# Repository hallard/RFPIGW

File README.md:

RFM12B RFM69CW Raspberry Pi Gateway With OLED and OOK
=====================================================

This is a simple board to be able to 
- Receive RFM12B data
- Receive RFM69CW data
- Blink 1st led when receiving from 1st module
- Blink 2nd led when receiving from 2nd module
- Display whatever on I2C OLED LCD
- Ready for OOK send/receive (see [jeelabs][5] for how to)

This is the 2nd proto board, I've ordered one on OSHPark, assembled 
then and it works fine so far. In this new version I've flipped the 
OLED since on some enclosure it was impossible to close them due to 
the total thickness of the board + OLED over it.

This version replace the 1.1 version which had some wiring reversed 
(MOSI/MISO) on the bottom module. I've also put the crystal on top 
side of the PCB instead of the bottom

No firmware or documentation is released because I'm currently working on 
project that will use this board as a gateway and I will release all source
code and documentation in the same time.
But you can take a look to this new project [Ultra Low Power Wireless Arduino Node][3]

This board gateway should work with the official firmware of [RFM2PI][6]
board dedicated for emoncms with small tweaking.

Check out news and other projects on my [blog][4]

Detailed Description
====================

Everything will be documented on my [blog][4]

**Schematic**  

**Boards**  
&nbsp;
&nbsp;

[3]: http://hallard.me/bp-ulpnode/
[4]: http://hallard.me
[5]: http://jeelabs.net/projects/cafe/wiki/Receiving_OOKASK_with_a_modified_RFM12B
[6]: http://wiki.openenergymonitor.org/index.php?title=RFM12Pi_V2

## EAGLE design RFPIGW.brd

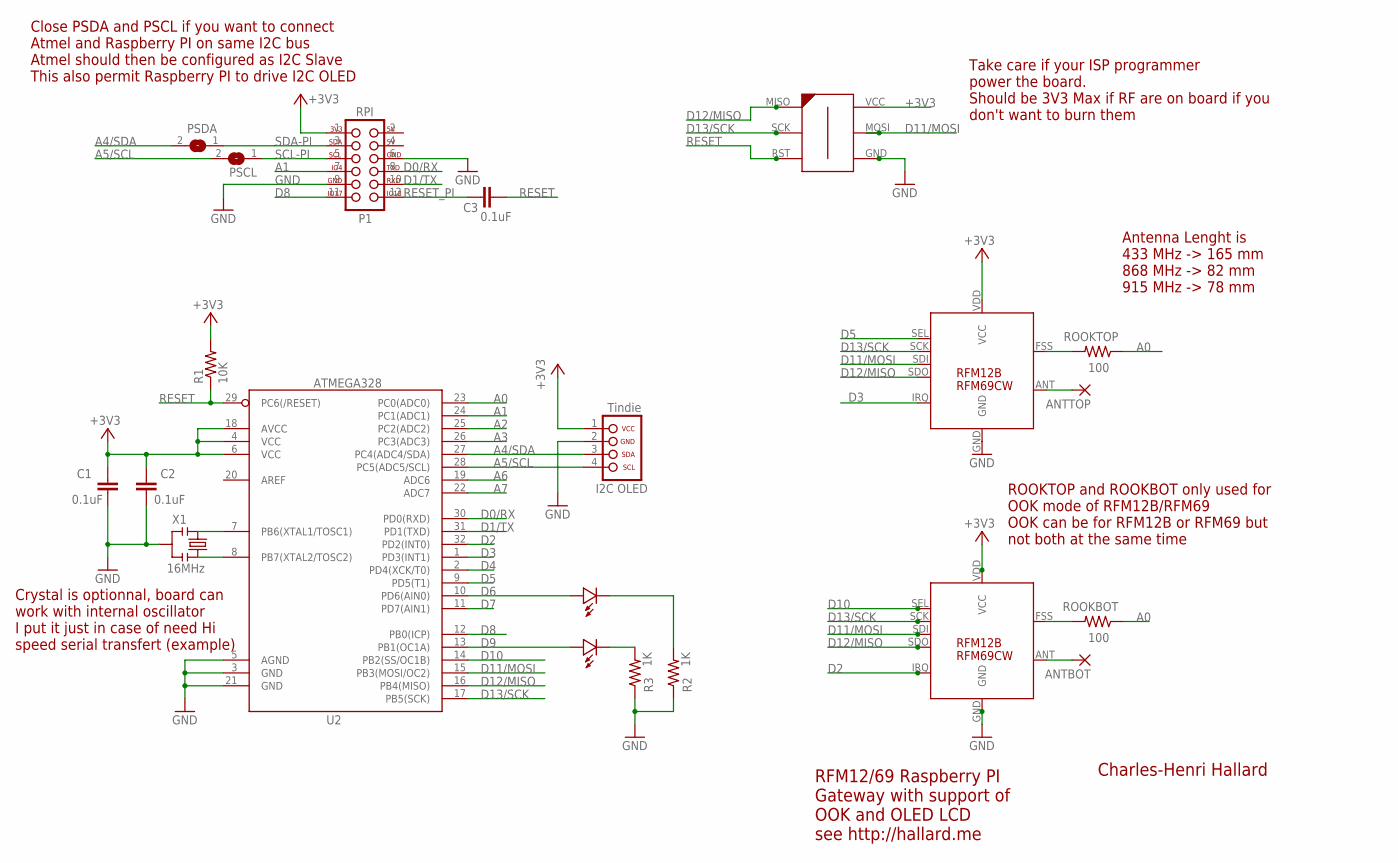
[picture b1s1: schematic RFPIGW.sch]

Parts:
ANTBOT: 1,6/0,8
ANTTOP: 1,6/0,8
C1, C2, C3: 0.1uF; 0805-CAP
LED1, LED2: LED0805-LARGE; 0805-LED-LARGEPADS
OLED: OLED_I2C_TINDIE; 1X04_NO_LOCK
PSCL: SJ
PSDA: SJ
R1: 10K; 0805-RES
R2, R3: 1K; 0805-RES
ROOKBOT: 100; 0805-RES
ROOKTOP: 100; 0805-RES
U2: ATMEGA328; TQFP32-08
U$1: PI P1; 2X06_LOCK
U$2, U$3: RFM12B; RFM12B-MINPADS
U$4: AVR-ISP-6-EDGE; 6PAD_ISP
X1: 16MHz; RESONATOR-SMD

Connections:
2: U$1.2
4: U$1.4
+3V3: C1.1, C2.1, OLED.1 (VCC), R1.2, U2.4 (VCC), U2.6 (VCC), U2.18 (AVCC), U$1.1, U$2.VDD (VCC), U$3.VDD (VCC), U$4.VCC
A0: ROOKBOT.1, ROOKTOP.1, U2.23 (PC0(ADC0))
A1: U2.24 (PC1(ADC1)), U$1.7
A2: U2.25 (PC2(ADC2))
A3: U2.26 (PC3(ADC3))
A4/SDA: OLED.3 (SDA), PSDA.2, U2.27 (PC4(ADC4/SDA))
A5/SCL: OLED.4 (SCL), PSCL.2, U2.28 (PC5(ADC5/SCL))
A6: U2.19 (ADC6)
A7: U2.22 (ADC7)
D0/RX: U2.30 (PD0(RXD)), U$1.8
D1/TX: U2.31 (PD1(TXD)), U$1.10
D2: U2.32 (PD2(INT0)), U$2.IRQ
D3: U2.1 (PD3(INT1)), U$3.IRQ
D4: U2.2 (PD4(XCK/T0))
D5: U2.9 (PD5(T1)), U$3.SEL
D6: LED2.PLUS, U2.10 (PD6(AIN0))
D7: U2.11 (PD7(AIN1))
D8: U2.12 (PB0(ICP)), U$1.11
D9: LED1.PLUS, U2.13 (PB1(OC1A))
D10: U2.14 (PB2(SS/OC1B)), U$2.SEL
D11/MOSI: U2.15 (PB3(MOSI/OC2)), U$2.SDI, U$3.SDI, U$4.MOSI
D12/MISO: U2.16 (PB4(MISO)), U$2.SDO, U$3.SDO, U$4.MISO
D13/SCK: U2.17 (PB5(SCK)), U$2.SCK, U$3.SCK, U$4.SCK
GND: C1.2, C2.2, OLED.2 (GND), R2.1, R3.1, U2.3 (GND), U2.5 (AGND), U2.21 (GND), U$1.6, U$1.9, U$2.GND, U$3.GND, U$4.GND, X1.2
unnamed: ROOKBOT.2, U$2.FSS (FFS)
unnamed: ANTTOP.1, U$3.ANT
unnamed: LED1.MINUS, R3.2
unnamed: ROOKTOP.2, U$3.FSS (FFS)
unnamed: U2.7 (PB6(XTAL1/TOSC1)), X1.1
unnamed: ANTBOT.1, U$2.ANT
unnamed: U2.8 (PB7(XTAL2/TOSC2)), X1.3
unnamed: LED2.MINUS, R2.2
RESET: C3.2, R1.1, U2.29 (PC6(/RESET)), U$4.RST
RESET_PI: C3.1, U$1.12
SCL-PI: PSCL.1, U$1.5
SDA-PI: PSDA.1, U$1.3

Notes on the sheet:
RFM12/69 Raspberry PI Gateway with support of OOK and OLED LCD see http://hallard.me
Charles-Henri Hallard
Antenna Lenght is 433 MHz -> 165 mm 868 MHz -> 82 mm 915 MHz -> 78 mm
ROOKTOP and ROOKBOT only used for OOK mode of RFM12B/RFM69 OOK can be for RFM12B or RFM69 but not both at the same time
Close PSDA and PSCL if you want to connect Atmel and Raspberry PI on same I2C bus Atmel should then be configured as I2C Slave This also permit Raspberry PI to drive I2C OLED
Take care if your ISP programmer power the board. Should be 3V3 Max if RF are on board if you don't want to burn them
Crystal is optionnal, board can work with internal oscillator I put it just in case of need Hi speed serial transfert (example)
RFM69CW

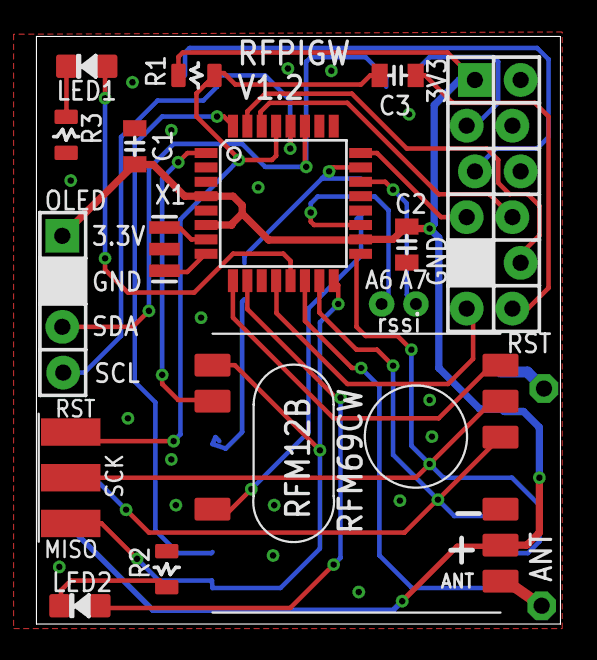
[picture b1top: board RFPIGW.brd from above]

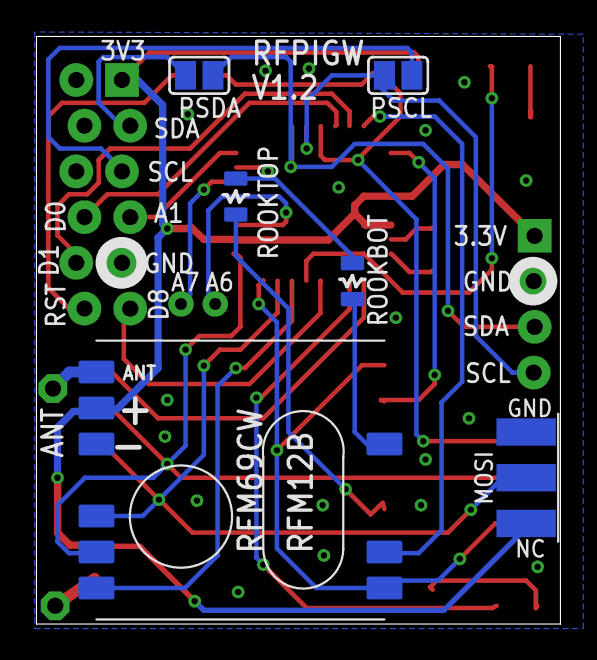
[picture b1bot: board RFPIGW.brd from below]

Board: 2 copper layers, 29.1 x 32.6 mm, 21 parts (5 on the bottom side), 30 nets.

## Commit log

2014-02-13 Creation
    First Commit, PCB and Stencil sent to FAB with this version
2014-02-13 Corrected link error
2014-02-13 Minor Fix
2014-09-25 Updated to V1.2
2014-09-25 test
2014-09-25 Image Resizing
2014-09-25 Image alignement
2014-09-25 Image Placement
2014-09-25 Images Fit to Github

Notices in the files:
parts and their libraries:
SparkFun-FreqCtrl: Licensing: CC v3.0 Share-Alike You are welcome to use this library for commercial purposes.
